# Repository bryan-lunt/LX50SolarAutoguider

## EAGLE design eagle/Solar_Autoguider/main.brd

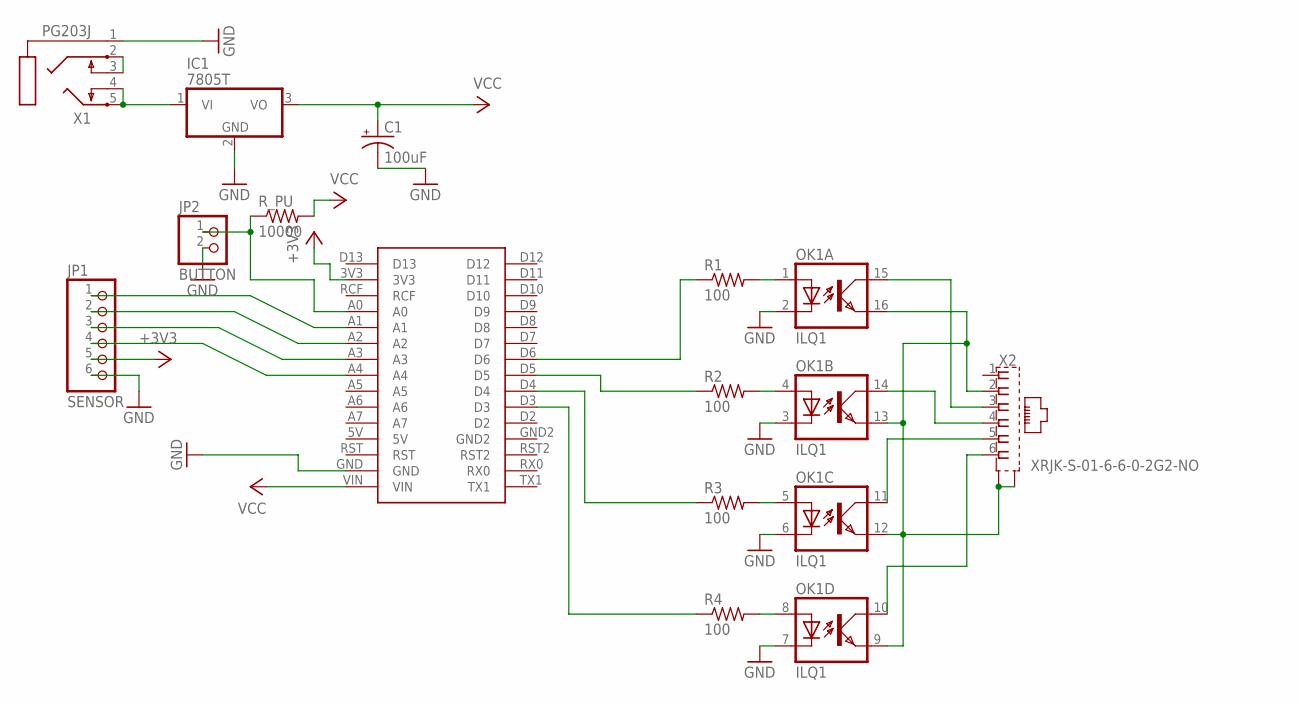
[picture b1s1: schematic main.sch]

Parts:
C1: 100uF; E2,5-6E
IC1: 7805T; TO220H; MPN LM7805CT
JP1: SENSOR; 1X06
JP2: BUTTON; 1X02
OK1: ILQ1; DIL16
R1, R2, R3, R4: 100; 0207/7
R_PU: 10000; 0207/7
U$1: ARDUINO_NANO_DEV; NANO_PACK
X1: PG203J
X2: XRJK-S-01-6-6-0-2G2-NO

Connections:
+3V3: JP1.5, U$1.3V3
GND: C1.-, IC1.2 (GND), JP1.6, JP2.2, OK1.2 (C), OK1.3 (C), OK1.6 (C), OK1.7 (C), U$1.GND, X1.1
unnamed: OK1.1 (A), R1.2
unnamed: OK1.4 (A), R2.2
unnamed: OK1.5 (A), R3.2
unnamed: OK1.8 (A), R4.2
unnamed: OK1.10 (COL), X2.6
unnamed: OK1.11 (COL), X2.5
unnamed: OK1.14 (COL), X2.4
unnamed: OK1.15 (COL), X2.3
unnamed: OK1.9 (EMIT), OK1.12 (EMIT), OK1.13 (EMIT), OK1.16 (EMIT), X2.2, X2.S1 (S), X2.S2 (S)
unnamed: JP1.1, U$1.A1
unnamed: JP1.2, U$1.A2
unnamed: JP1.3, U$1.A3
unnamed: JP1.4, U$1.A4
unnamed: IC1.1 (VI), X1.4, X1.5
unnamed: JP2.1, R_PU.1, U$1.A0
unnamed: R4.1, U$1.D3
unnamed: R3.1, U$1.D4
unnamed: R2.1, U$1.D5
unnamed: R1.1, U$1.D6
unnamed: X1.2, X1.3
VCC: C1.+, IC1.3 (VO), R_PU.2, U$1.VIN

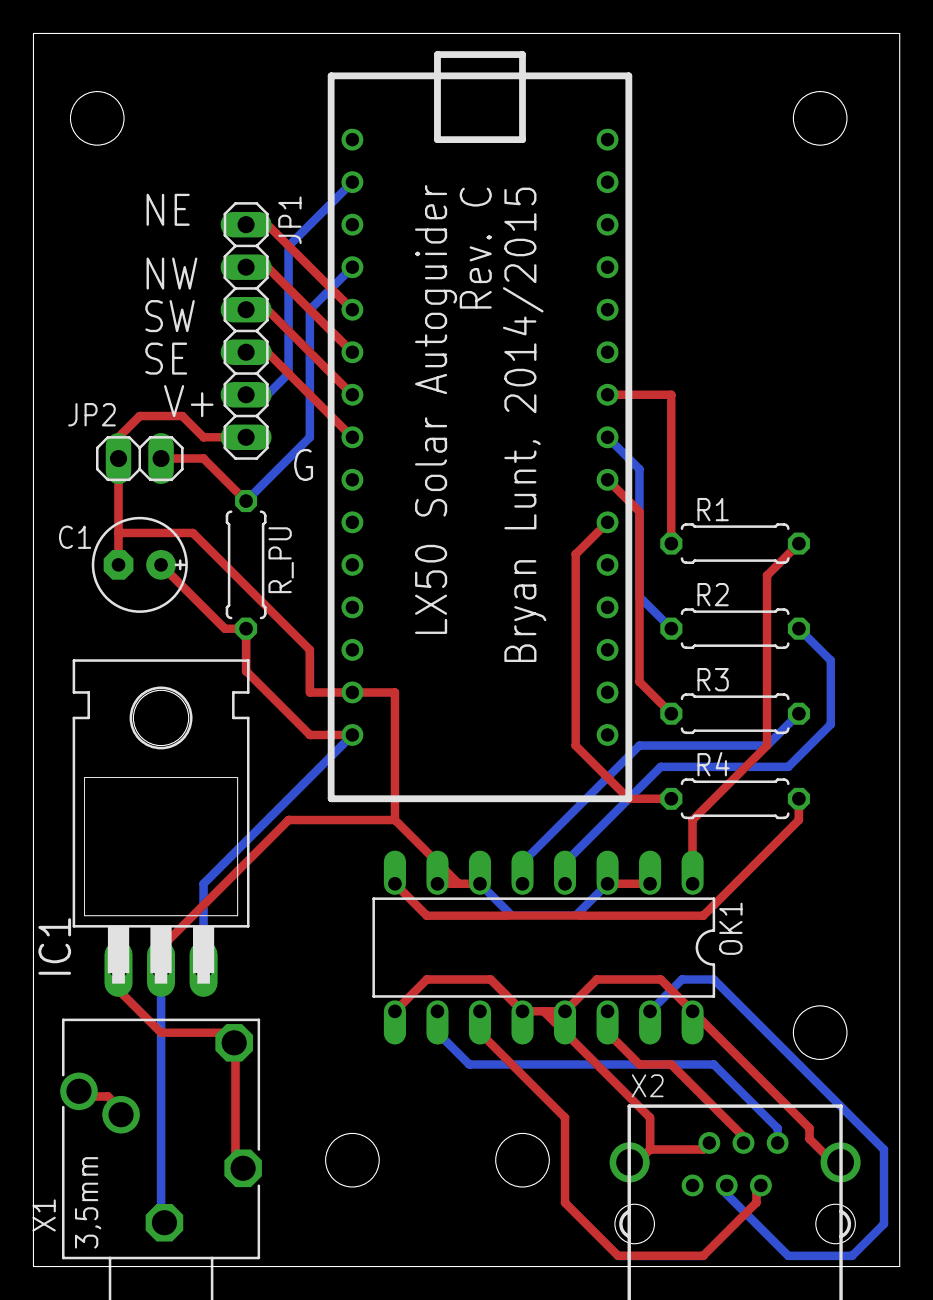
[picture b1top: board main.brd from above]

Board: 2 copper layers, 51.7 x 73.7 mm, 13 parts (0 on the bottom side), 23 nets.

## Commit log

2014-11-30 Imported code and models.
2014-11-30 mostly self-contained now?
2014-11-30 Improved Arduino nano symbol
2014-11-30 Better silk-screen on board.
2015-01-06 Altered program to work with board.
2015-03-25 Finalized housing design.
